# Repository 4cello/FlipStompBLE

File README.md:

# FlipStompBLE

## Firmware
## PCB

## Enclosure

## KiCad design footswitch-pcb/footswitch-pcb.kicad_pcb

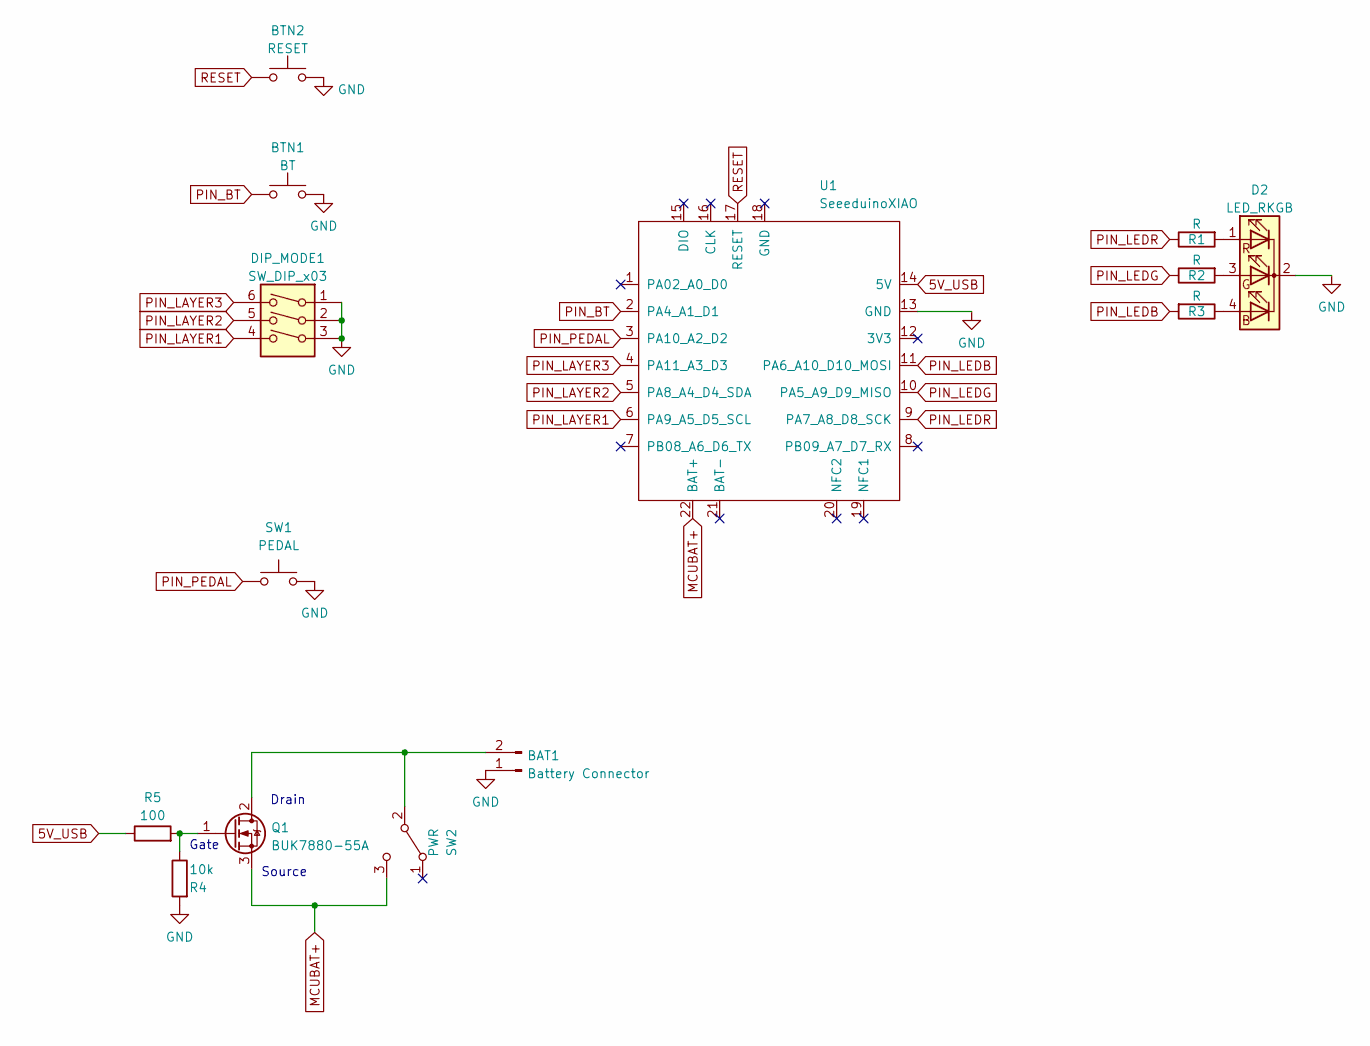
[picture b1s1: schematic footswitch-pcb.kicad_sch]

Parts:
BAT1: Battery Connector; JST_XH_S2B-XH-A-1_1x02_P2.50mm_Horizontal
BTN1: BT; SW_Tactile_SPST_Angled_PTS645Vx39-2LFS
BTN2: RESET; SW_PUSH_6mm_H7.3mm
D2: LED_RKGB; LED_D5.0mm-4_RGB_Wide_Pins
DIP_MODE1: SW_DIP_x03; SW_DIP_SPSTx03_Slide_6.7x9.18mm_W7.62mm_P2.54mm_LowProfile
Q1: BUK7880-55A; SOT-23
R1, R2, R3: R; R_1206_3216Metric_Pad1.30x1.75mm_HandSolder
R4: 10k; R_1206_3216Metric_Pad1.30x1.75mm_HandSolder
R5: 100; R_1206_3216Metric_Pad1.30x1.75mm_HandSolder
SW1: PEDAL; SW_Cherry_MX_1.00u_PCB
SW2: PWR; SW_Slide_1P2T_CK_OS102011MS2Q
U1: SeeeduinoXIAO; XIAO-nRF52840-Sense-14P-2.54-21X17.8MM

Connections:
5V_USB: R5.1, U1.14 (5V)
GND: BAT1.1, BTN1.2, BTN2.2, D2.2 (K), DIP_MODE1.1, DIP_MODE1.2, DIP_MODE1.3, R4.2, SW1.2, U1.13 (GND)
MCUBAT+: Q1.3 (S), SW2.3 (C), U1.22 (BAT+)
unnamed: BAT1.2, Q1.2 (D), SW2.2 (B)
unnamed: D2.1 (RA), R1.2
unnamed: D2.3 (GA), R2.2
unnamed: Q1.1 (G), R4.1, R5.2
unnamed: D2.4 (BA), R3.1
PIN_BT: BTN1.1, U1.2 (PA4_A1_D1)
PIN_LAYER1: DIP_MODE1.4, U1.6 (PA9_A5_D5_SCL)
PIN_LAYER2: DIP_MODE1.5, U1.5 (PA8_A4_D4_SDA)
PIN_LAYER3: DIP_MODE1.6, U1.4 (PA11_A3_D3)
PIN_LEDB: R3.2, U1.11 (PA6_A10_D10_MOSI)
PIN_LEDG: R2.1, U1.10 (PA5_A9_D9_MISO)
PIN_LEDR: R1.1, U1.9 (PA7_A8_D8_SCK)
PIN_PEDAL: SW1.1, U1.3 (PA10_A2_D2)
RESET: BTN2.1, U1.17 (RESET)

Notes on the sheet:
Gate
Source
Drain

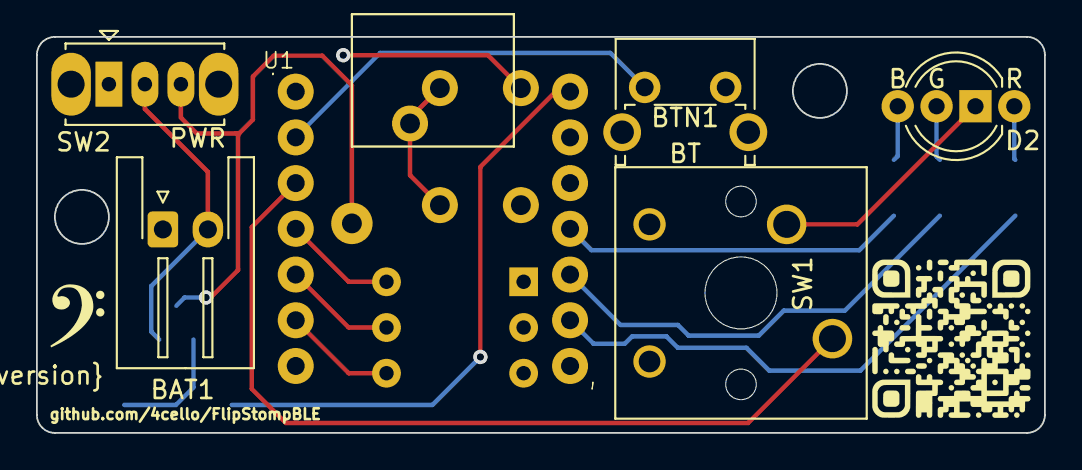
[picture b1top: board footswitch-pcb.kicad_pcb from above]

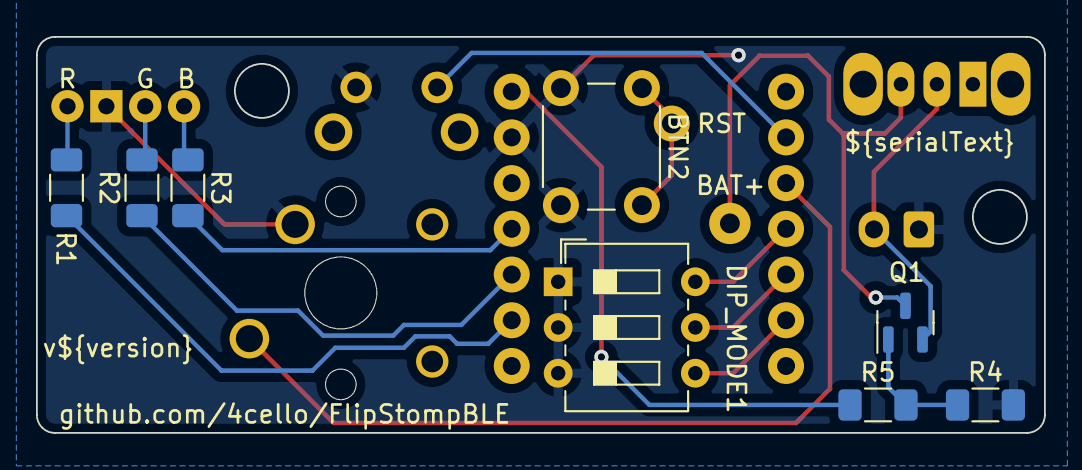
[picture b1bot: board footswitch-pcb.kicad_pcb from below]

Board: 2 copper layers, 56.0 x 22.0 mm, 14 parts (8 on the bottom side), 17 nets.

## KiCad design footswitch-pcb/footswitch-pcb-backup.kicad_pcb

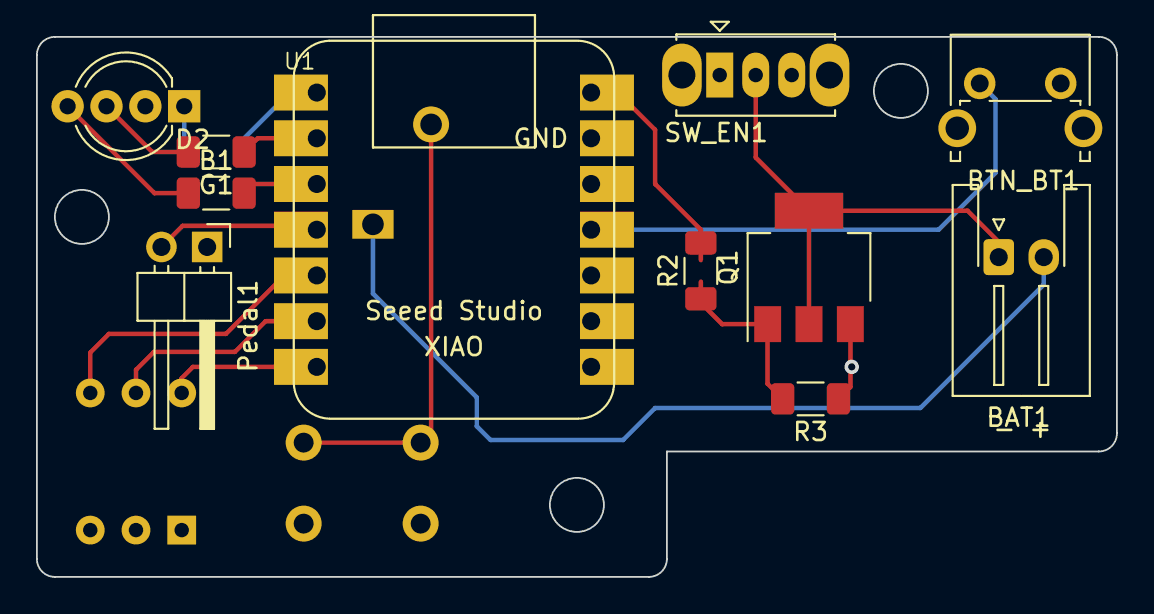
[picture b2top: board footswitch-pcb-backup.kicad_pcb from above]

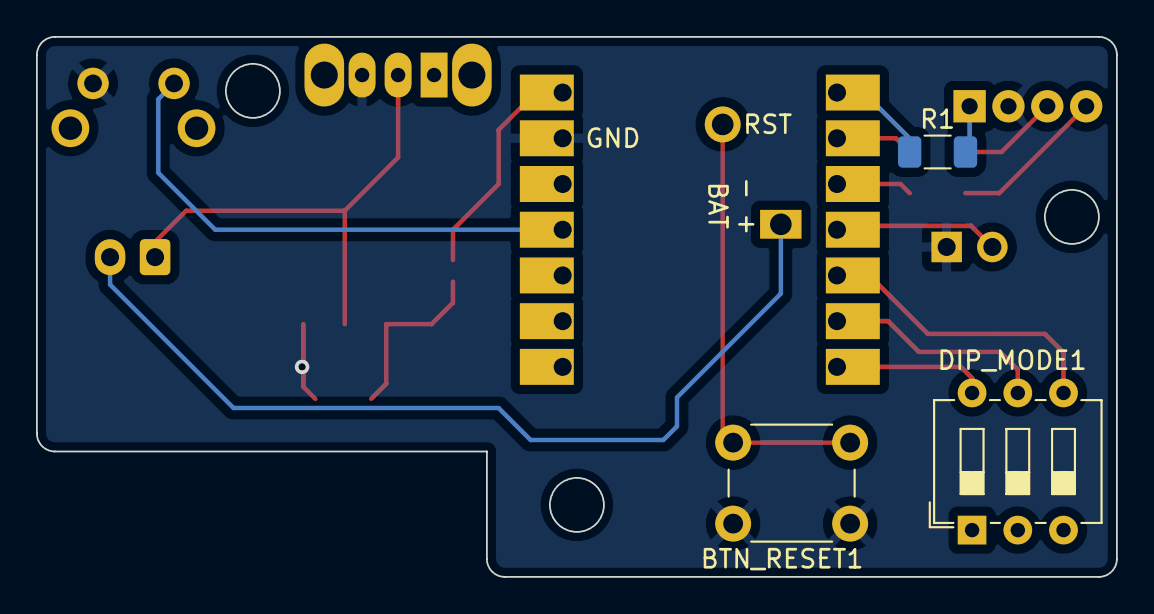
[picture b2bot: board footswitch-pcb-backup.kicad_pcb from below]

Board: 2 copper layers, 60.0 x 30.0 mm, 14 parts (3 on the bottom side), 18 nets.

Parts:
B1: R; R_1206_3216Metric_Pad1.30x1.75mm_HandSolder
BAT1: Battery Connector; JST_XH_S2B-XH-A-1_1x02_P2.50mm_Horizontal
BTN_BT1: BTN_BLUETOOTH; SW_Tactile_SPST_Angled_PTS645Vx39-2LFS
BTN_RESET1: BTN_RESET; SW_PUSH_6mm_H7.3mm
D2: LED_RKGB; LED_D5.0mm-4_RGB_Wide_Pins
DIP_MODE1: SW_DIP_x03; SW_DIP_SPSTx03_Slide_6.7x9.18mm_W7.62mm_P2.54mm_LowProfile
G1: R; R_1206_3216Metric_Pad1.30x1.75mm_HandSolder
Pedal1: Conn_Pedal; PinHeader_1x02_P2.54mm_Horizontal
Q1: BUK7880-55A; SOT-223-3_TabPin2
R1: R; R_1206_3216Metric_Pad1.30x1.75mm_HandSolder
R2: 100; R_1206_3216Metric_Pad1.30x1.75mm_HandSolder
R3: 10k; R_1206_3216Metric_Pad1.30x1.75mm_HandSolder
SW_EN1: SW_ENABLE; SW_Slide_1P2T_CK_OS102011MS2Q
U1: SeeeduinoXIAO; XIAO-nRF52840-Sense-14P-2.54-21X17.8MM

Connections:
5V_USB: R2.2, U1.14 (5V)
BAT+: BAT1.2, U1.22 (BAT+)
GND: BTN_BT1.2, BTN_RESET1.2, D2.2 (K), Pedal1.1, Q1.3 (S), R3.1, SW_EN1.3 (C), U1.13 (GND)
GNDS: DIP_MODE1.1, DIP_MODE1.2, DIP_MODE1.3
unnamed: B1.1, D2.4 (BA)
unnamed: BAT1.1, Q1.2 (D), SW_EN1.2 (B)
unnamed: D2.1 (RA), R1.2
unnamed: D2.3 (GA), G1.2
unnamed: Q1.1 (G), R2.1, R3.2
PIN_BT: BTN_BT1.1, U1.11 (PA6_A10_D10_MOSI)
PIN_LAYER1: DIP_MODE1.4, U1.5 (PA8_A4_D4_SDA)
PIN_LAYER2: DIP_MODE1.5, U1.6 (PA9_A5_D5_SCL)
PIN_LAYER3: DIP_MODE1.6, U1.7 (PB08_A6_D6_TX)
PIN_LEDB: B1.2, U1.3 (PA10_A2_D2)
PIN_LEDG: G1.1, U1.2 (PA4_A1_D1)
PIN_LEDR: R1.1, U1.1 (PA02_A0_D0)
PIN_PEDAL: Pedal1.2, U1.4 (PA11_A3_D3)
RESET: BTN_RESET1.1, U1.17 (RESET)

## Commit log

2023-01-07 Initial User Config.
2023-01-07 First attempts
2023-01-07 Added kscan
2023-01-07 Added hummingbird shield, maybe it works?
2023-01-07 Matrix transform workaround?
2023-01-07 fixed typo
2023-01-07 swapped row and column
2023-01-07 renamed files
2023-01-07 removed argument
2023-01-07 Added include, changed BLE name
2023-01-07 Removed a weird section
2023-01-07 re-added parameter!
2023-01-07 added missing semicolon
2023-01-07 Removed rows and columns
2023-01-08 Experiment with hold-tap
2023-01-08 Changed ht_hp for mt in config but not in keymap
2023-01-08 replaced ht_hp in keymap
2023-01-08 Bluetooth button rework?
2023-01-08 Changed list
2023-01-08 Removed hold from tap dance
2023-01-08 Re-added up-down-layer
2023-01-08 Moved comments to separate lines
2023-01-08 ACTUALLY changed to up/down in the up-down-layer
2023-01-08 Another attempt at the tapdance-hold
2023-01-08 Backlight test
2023-01-08 Added GPIO_ACTIVE_HIGH
2023-01-08 Changed Backlight LED pin from built-in to external pin
2023-01-08 added import
2023-01-08 Macro workaround for tap-hold dance
2023-01-08 Another attempt
2023-01-08 ANOTHER attempt, this time for real
2023-01-08 Another attempt, now with 2 macros
2023-01-08 Added missing(?) parameters to bt_ht
2023-01-08 Removed backlight experiments, oops
2023-01-08 Removed BT_CLR from tap dance
2023-01-08 cleanup
2023-01-08 gitignore
2023-01-09 PCB Update
2023-01-13 Changed pins to final(?)
2023-01-14 Multi-Layer test
2023-01-14 Another Multi-Layer test
2023-01-14 Fixed layer change keys
2023-01-14 Added layer keybindings
2023-01-14 Changed BT pin, increased hold duration (hopefully)
2023-01-18 Conditional layers
2023-01-18 Modified GHA to only run on config changes, hopefully
2023-01-18 Comments in keymap, power MOSFET in schematic
2023-01-25 MOSFET?
2023-01-25 THT Pogo Pins
2023-01-31 Possibly final version of PCB?
2023-02-03 v1.0?
2023-02-03 Replaced config with ZMK submodule
2023-02-03 Removed GHA
2023-02-03 More cleanup
2023-02-05 Updated ZMK firmware
2023-03-20 Onboard Cherry Switch
2023-03-20 Small cosmetic changes
2023-07-31 Modified new PCB
2023-11-24 Update ZMK
2024-05-17 ZMK merge???
2024-05-17 Added working firmware file
